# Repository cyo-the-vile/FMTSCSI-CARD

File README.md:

# FMTSCSI-CARD
PCB to use an internal SCSI device such as a hard drive.

I will warn you this is absolutely untested but I'm confident it should work.
Connector is based on Labo-san's research for SCSI devices and it looks like it matches my hard drive tray for my FMT FRESH.

The connectors for SCSI and FMT must be right angle connectors. 

Connectors must be 2.54mm pitch, right angle, 50 pin, 2 row.

One connector you can use for FMT side is part number: 30350-5002HB

One connector you can use for SCSI side is part number: 66527-025LF

However there are other parts you can use that could be cheaper and available.

The voltage receptables are labeled if you wanted to use a mechanical hard drive.  I would expect in 2021, everyone uses hard drive emulators.

Please contact me on twitter if there is any questions or trouble  @cyothevile

To get PCB created, take the V1 Card.zip to a factory.

＃FMTSCSI-CARD
ハードドライブなどの内蔵SCSIデバイスを使用するPCB。

日本人の友達、これは機械翻訳です。ご不明な点がございましたらご連絡ください。私のツイッターアカウント：cyothevile。

これは完全にテストされていないことを警告しますが、動作するはずです。
コネクタは、LaboさんのSCSIデバイスの調査に基づいており、FMTFRESHのハードドライブトレイと一致しているようです。

SCSIおよびFMTのコネクタは、直角コネクタである必要があります。

コネクタは、2.54mmピッチ、直角、50ピン、2列である必要があります。

FMT側に使用できるコネクタの1つは、部品番号：30350-5002HBです。

SCSI側に使用できるコネクタの1つは、部品番号：66527-025LFです。

ただし、他にも安価で入手可能な部品があります。

機械式ハードドライブを使用する場合は、許容電圧にラベルが付けられています。 2021年には、誰もがハードドライブエミュレーターを使用すると思います。

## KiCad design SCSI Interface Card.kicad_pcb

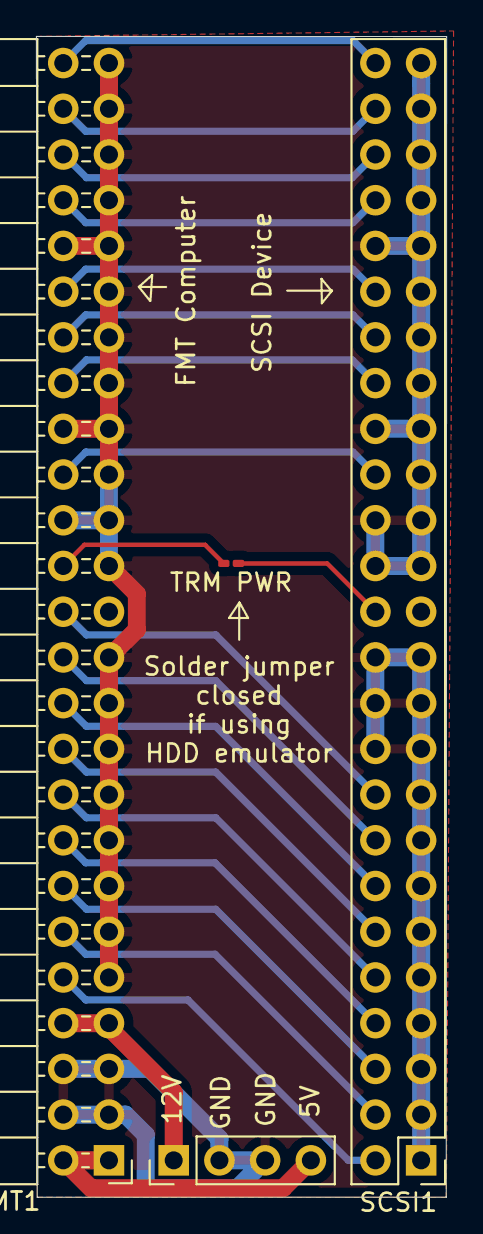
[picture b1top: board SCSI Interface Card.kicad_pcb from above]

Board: 2 copper layers, 22.8 x 64.5 mm, 4 parts (0 on the bottom side), 22 nets.

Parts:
FMT1: Conn_02x25_Odd_Even; PinHeader_2x25_P2.54mm_Horizontal
PWR1: Conn_01x04; PinHeader_1x04_P2.54mm_Vertical
SCSI1: Conn_02x25_Odd_Even; PinHeader_2x25_P2.54mm_Vertical
TRM PWR: Conn_01x02_Male; C_0201_0603Metric_Pad0.64x0.40mm_HandSolder

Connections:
/5V: FMT1.1, FMT1.2, PWR1.4
/12V: FMT1.7, FMT1.8, PWR1.1
/ACK: FMT1.38, SCSI1.38
/ATN: FMT1.32, SCSI1.32
/BSY: FMT1.36, SCSI1.36
/CD: FMT1.46, SCSI1.46
/DB0: FMT1.10, SCSI1.2
/DB1: FMT1.12, SCSI1.4
/DB2: FMT1.14, SCSI1.6
/DB3: FMT1.16, SCSI1.8
/DB4: FMT1.18, SCSI1.10
/DB5: FMT1.20, SCSI1.12
/DB6: FMT1.22, SCSI1.14
/DB7: FMT1.24, SCSI1.16
/DBP: FMT1.26, SCSI1.18
/IO: FMT1.50, SCSI1.50
/REQ: FMT1.48, SCSI1.48
/RST: FMT1.40, SCSI1.40
/SEL: FMT1.44, SCSI1.44
/TRM_1: SCSI1.26, TRM PWR.1
/TRM_2: FMT1.28, TRM PWR.2
GND: FMT1.3, FMT1.4, FMT1.5, FMT1.6, FMT1.9, FMT1.11, FMT1.13, FMT1.15, FMT1.17, FMT1.19, FMT1.21, FMT1.23, FMT1.27, FMT1.29, FMT1.30, FMT1.31, FMT1.33, FMT1.34, FMT1.35, FMT1.37, FMT1.39, FMT1.41, FMT1.42, FMT1.43, FMT1.45, FMT1.47, FMT1.49, PWR1.2, PWR1.3, SCSI1.1, SCSI1.3, SCSI1.5, SCSI1.7, SCSI1.9, SCSI1.11, SCSI1.13, SCSI1.15, SCSI1.17, SCSI1.19, SCSI1.20, SCSI1.21, SCSI1.22, SCSI1.23, SCSI1.24, SCSI1.27, SCSI1.28, SCSI1.29, SCSI1.30, SCSI1.31, SCSI1.33, SCSI1.34, SCSI1.35, SCSI1.37, SCSI1.39, SCSI1.41, SCSI1.42, SCSI1.43, SCSI1.45, SCSI1.47, SCSI1.49

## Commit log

2021-07-31 Initial Commit
    V1 commit
2021-07-31 Update README.md
    Initial Commit
